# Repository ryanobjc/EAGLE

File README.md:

# EAGLE

A template eagle directory for Code Next Fall 2019 class in PCB design.

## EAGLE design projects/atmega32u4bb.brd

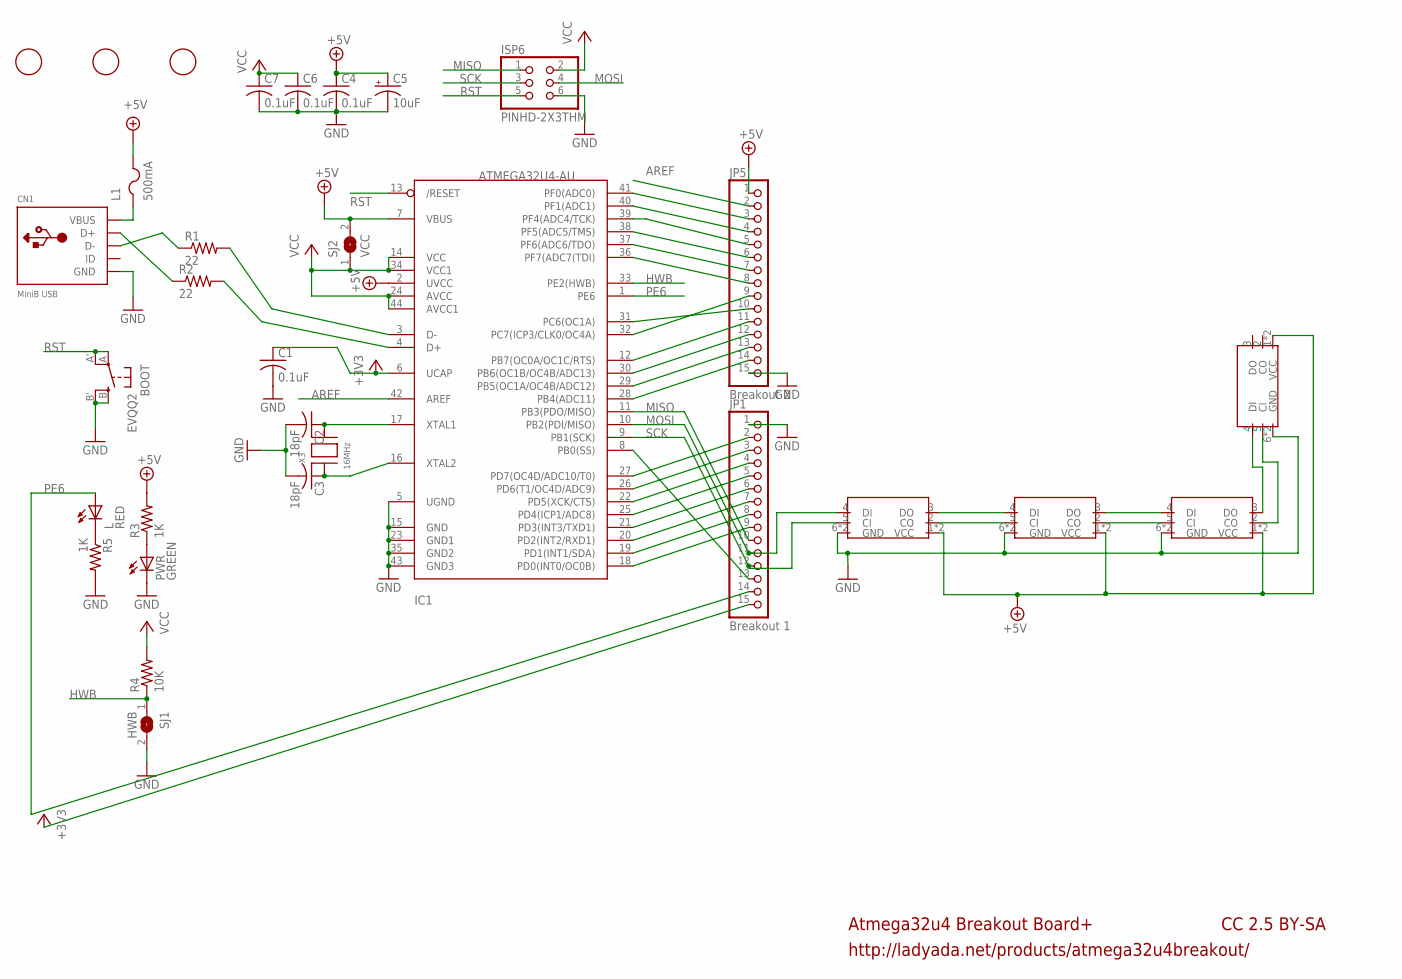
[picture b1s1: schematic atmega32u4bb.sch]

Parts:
BOOT: EVQQ2; EVQ-Q2
C1, C4, C6, C7: 0.1uF; C0805K
C2, C3: 18pF; C0805K
C5: 10uF; A/3216-18R
CN1: MiniB USB; USB-MINIB
IC1: ATMEGA32U4-AU; TQFP44
ISP6: PINHD-2X3THM; ISP6
JP1: Breakout 1; 1X15-CB
JP5: Breakout 2; 1X15-CB
L: RED; CHIPLED_0805
L1: 500mA; R1206
PWR: GREEN; CHIPLED_0805
R1, R2: 22; R0805
R3, R5: 1K; R0805
R4: 10K; R0805
SJ1: HWB; SJ
SJ2: VCC; SJ
U$1, U$2, U$6: FIDUCIAL; FIDUCIAL_1MM
U$3, U$5, U$7, U$8: DOTSTAR2020; LED_3341
X3: 16MHz; NX5032

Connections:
+3V3: C1.1, IC1.6 (UCAP), JP1.15
+5V: C4.1, C5.+, IC1.2 (UVCC), IC1.7 (VBUS), JP5.1, L1.2, R3.2, SJ2.2, U$3.1 (VCC), U$3.8 (VCC), U$5.1 (VCC), U$5.8 (VCC), U$7.1 (VCC), U$7.8 (VCC), U$8.1 (VCC), U$8.8 (VCC)
AREF: IC1.42 (AREF), JP5.2
GND: BOOT.B (S), BOOT.B' (S1), C1.2, C2.2, C3.2, C4.2, C5.-, C6.2, C7.2, CN1.GND, IC1.5 (UGND), IC1.15 (GND), IC1.23 (GND1), IC1.35 (GND2), IC1.43 (GND3), ISP6.6, JP1.1, JP5.15, PWR.C, R5.2, SJ1.2, U$3.6 (GND), U$3.7 (GND), U$5.6 (GND), U$5.7 (GND), U$7.6 (GND), U$7.7 (GND), U$8.6 (GND), U$8.7 (GND)
HWB: IC1.33 (PE2(HWB)), R4.1, SJ1.1
MISO: IC1.11 (PB3(PDO/MISO)), ISP6.1, JP1.10
MOSI: IC1.10 (PB2(PDI/MISO)), ISP6.4, JP1.11, U$3.4 (DI)
unnamed: PWR.A, R3.1
unnamed: CN1.D+, R2.1
unnamed: IC1.3 (D-), R1.2
unnamed: IC1.4 (D+), R2.2
unnamed: CN1.D-, R1.1
unnamed: C2.1, IC1.17 (XTAL1), X3.P$2
unnamed: C3.1, IC1.16 (XTAL2), X3.P$1
unnamed: L.C, R5.1
unnamed: U$3.3 (DO), U$5.4 (DI)
unnamed: U$3.2 (CO), U$5.5 (CI)
unnamed: U$5.3 (DO), U$7.4 (DI)
unnamed: U$5.2 (CO), U$7.5 (CI)
unnamed: U$7.3 (DO), U$8.4 (DI)
unnamed: U$7.2 (CO), U$8.5 (CI)
PB0: IC1.8 (PB0(SS)), JP1.13
PB4: IC1.28 (PB4(ADC11)), JP5.14
PB5: IC1.29 (PB5(OC1A/OC4B/ADC12)), JP5.13
PB6: IC1.30 (PB6(OC1B/OC4B/ADC13)), JP5.12
PB7: IC1.12 (PB7(OC0A/OC1C/RTS)), JP5.11
PC6: IC1.31 (PC6(OC1A)), JP5.10
PC7: IC1.32 (PC7(ICP3/CLK0/OC4A)), JP5.9
PD0: IC1.18 (PD0(INT0/OC0B)), JP1.9
PD1: IC1.19 (PD1(INT1/SDA)), JP1.8
PD2: IC1.20 (PD2(INT2/RXD1)), JP1.7
PD3: IC1.21 (PD3(INT3/TXD1)), JP1.6
PD4: IC1.25 (PD4(ICP1/ADC8)), JP1.5
PD5: IC1.22 (PD5(XCK/CTS)), JP1.4
PD6: IC1.26 (PD6(T1/OC4D/ADC9)), JP1.3
PD7: IC1.27 (PD7(OC4D/ADC10/T0)), JP1.2
PE6: IC1.1 (PE6), JP1.14, L.A
PF0: IC1.41 (PF0(ADC0)), JP5.3
PF1: IC1.40 (PF1(ADC1)), JP5.4
PF4: IC1.39 (PF4(ADC4/TCK)), JP5.5
PF5: IC1.38 (PF5(ADC5/TMS)), JP5.6
PF6: IC1.37 (PF6(ADC6/TDO)), JP5.7
PF7: IC1.36 (PF7(ADC7(TDI)), JP5.8
RST: BOOT.A, BOOT.A' (P1), IC1.13 (/RESET), ISP6.5
SCK: IC1.9 (PB1(SCK)), ISP6.3, JP1.12, U$3.5 (CI)
VBUS: CN1.VBUS, L1.1
VCC: C6.1, C7.1, IC1.14 (VCC), IC1.24 (AVCC), IC1.34 (VCC1), IC1.44 (AVCC1), ISP6.2, R4.2, SJ2.1

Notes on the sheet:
Atmega32u4 Breakout Board+
http://ladyada.net/products/atmega32u4breakout/
CC 2.5 BY-SA

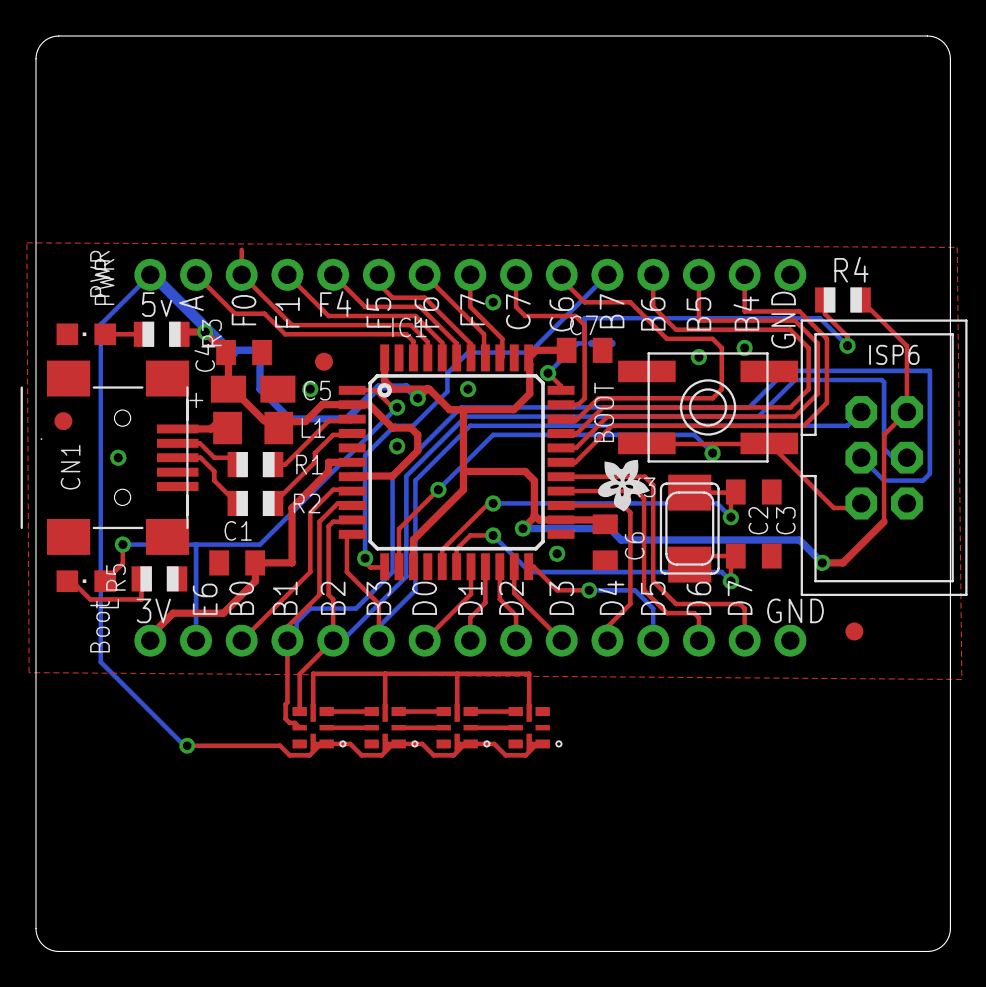
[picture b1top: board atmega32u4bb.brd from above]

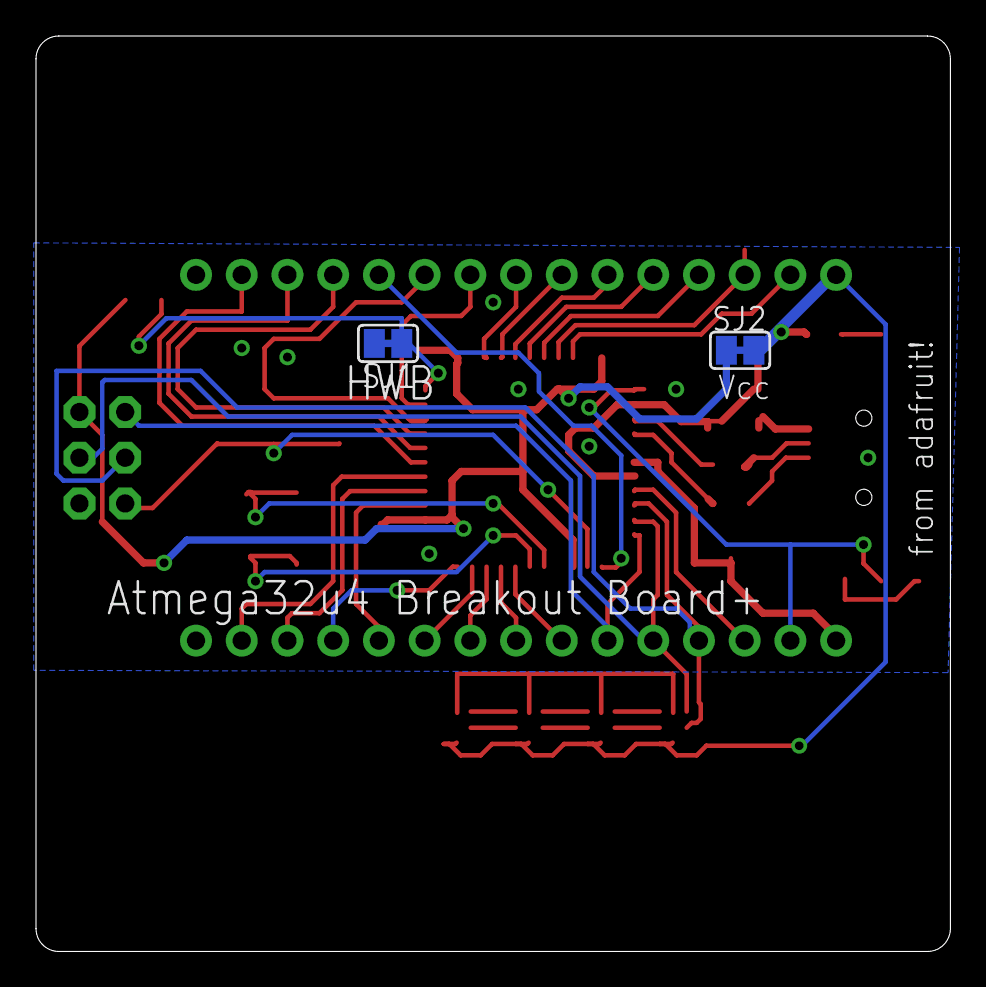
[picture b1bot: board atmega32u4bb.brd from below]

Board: 2 copper layers, 50.8 x 50.9 mm, 32 parts (2 on the bottom side), 47 nets.

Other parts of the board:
U$4: ADAFRUIT200MIL

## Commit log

2019-10-24 v1.0 of library, startup script, and use library script
2019-10-24 Readme
2019-11-12 Power switch
2019-11-13 Make the coin cell package boundaries visible
2020-02-04 import adafruit library
2020-02-04 atmega32u4 starter schematic and board
2020-02-05 prep for feb 5th class
2020-02-11 Add 2020 (2mm by 2mm) footprint for dotstar, updated example to use that footprint
